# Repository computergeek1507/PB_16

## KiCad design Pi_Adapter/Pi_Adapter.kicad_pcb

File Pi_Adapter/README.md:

# Copyright and Disclaimer
Copyright: Scott Hanson

This documentation describes Open Hardware and is licensed under the CERN OHL v. 1.2.

You may redistribute and modify this documentation under the terms of the CERN OHL v.1.2. (http://ohwr.org/cernohl). This documentation is distributed WITHOUT ANY EXPRESS OR IMPLIED WARRANTY, INCLUDING OF MERCHANTABILITY, SATISFACTORY QUALITY AND FITNESS FOR A PARTICULAR PURPOSE. Please see the CERN OHL v.1.2 for applicable conditions

# Pi Expansion

Expansion breakout for a Raspberry Pi. Open source applications were used to create this PCB. [KiCad](http://kicad.org/) was used for the PCB design, and [LibreOffice](https://www.libreoffice.org/) for the documentation.

To order your own PCB upload the gerber.zip file to your favorite PCB manufacture of choice, I personally use [jlcpcb.com](https://jlcpcb.com/).

### Features
* 16 Port Expansion
* OLED Display header
* 2 pin GPIO Header for Push Button or Relay Support
* 5v Header

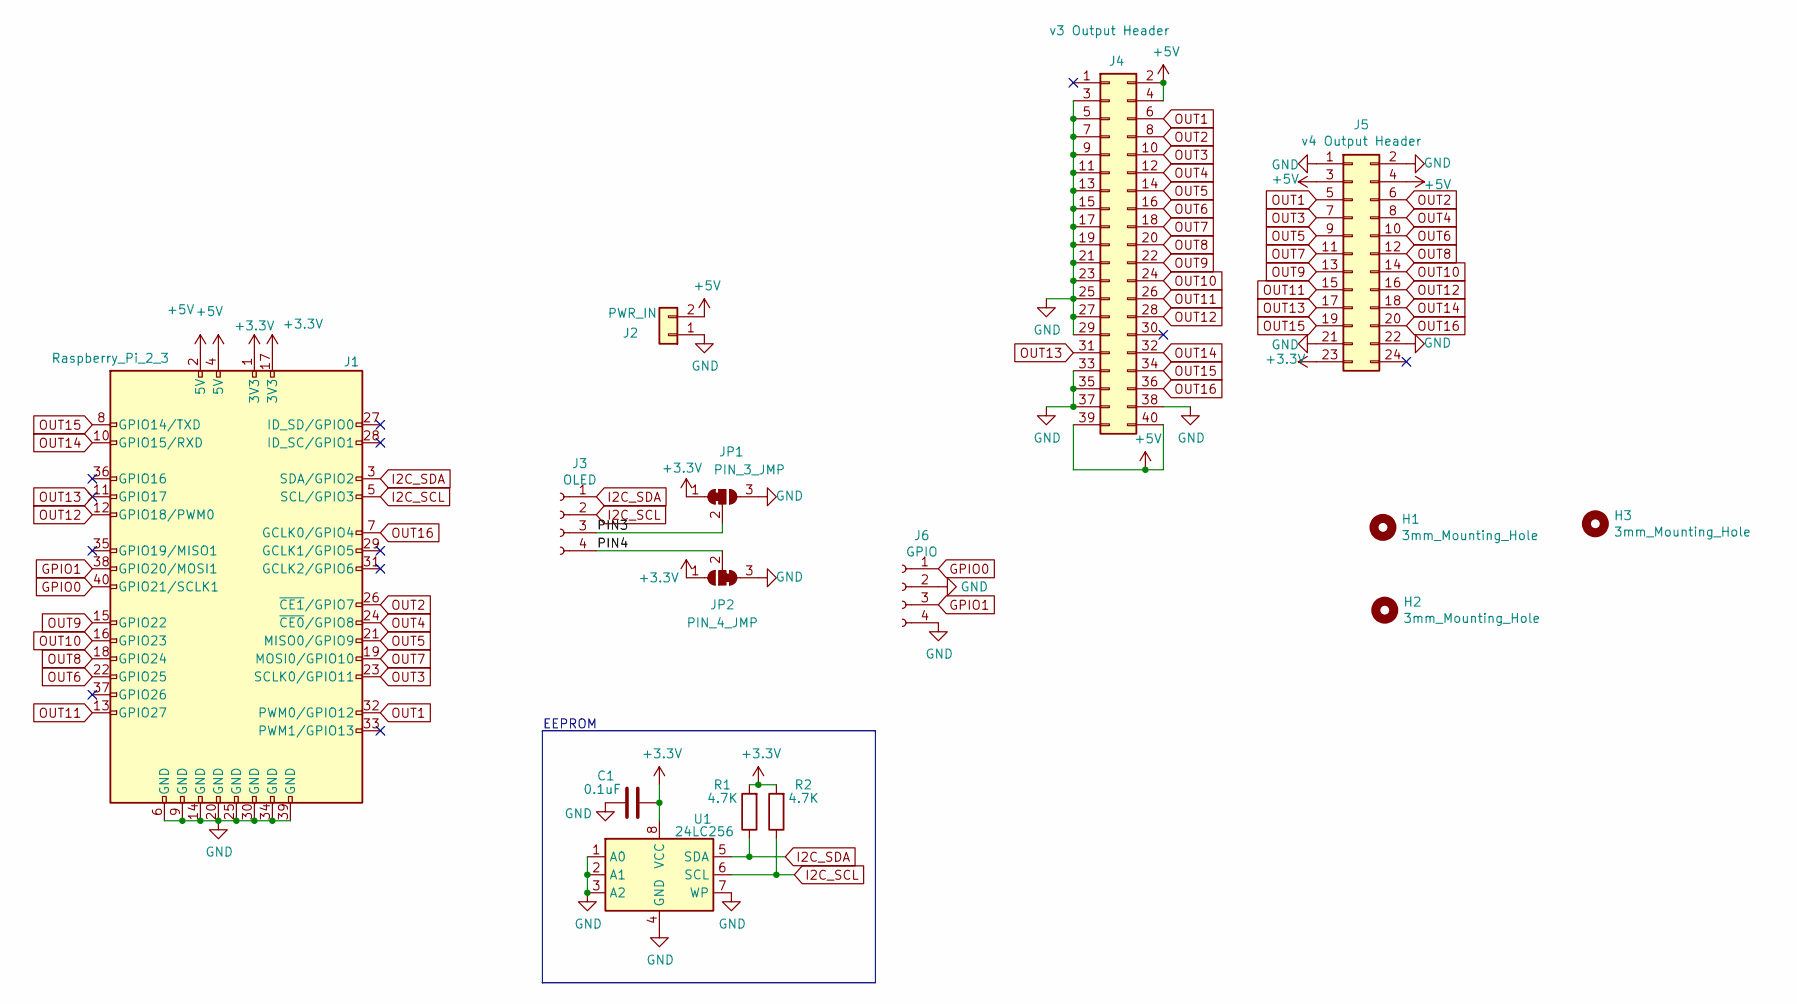
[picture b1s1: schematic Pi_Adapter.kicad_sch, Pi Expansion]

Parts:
C1: 0.1uF; C_0603_1608Metric_Pad1.08x0.95mm_HandSolder; MPN CL10B104KB8NNWC; Digi-Key_PN 1276-1935-2-ND
H1, H2, H3: 3mm_Mounting_Hole; MountingHole_3mm
J1: Raspberry_Pi_2_3; PinSocket_2x20_P2.54mm_Vertical; MPN PPPC202LFBN-RC; Digi-Key_PN S7123-ND
J2: PWR_IN; TerminalBlock_Phoenix_MKDS-1,5-2_1x02_P5.00mm_Horizontal; MPN ED2675-ND; Digi-Key_PN OSTT7020150
J3: OLED; PinSocket_1x04_P2.54mm_Vertical; MPN PPTC041LFBN-RC; Digi-Key_PN S7002-ND
J4: v3 Output Header; IDC-Header_2x20_P2.54mm_Vertical; MPN SBH11-PBPC-D20-ST-BK; Digi-Key_PN S9175-ND
J5: v4 Output Header; IDC-Header_2x12_P2.54mm_Vertical; MPN Z-S311024S1GK1A; Digi-Key_PN ED10525-ND
J6: GPIO; PinSocket_1x04_P2.54mm_Vertical; MPN PPTC041LFBN-RC; Digi-Key_PN S7002-ND
JP1: PIN_3_JMP; SolderJumper-3_P1mm_Bridged12
JP2: PIN_4_JMP; SolderJumper-3_P1mm_Bridged23
R1, R2: 4.7K; R_0603_1608Metric_Pad0.98x0.95mm_HandSolder; MPN RC0603JR-074K7L; Digi-Key_PN 311-4.7KGRCT-ND
U1: 24LC256; SOIC-8_3.9x4.9mm_P1.27mm; MPN 24LC256T-I/SN; Digi-Key_PN 24LC256T-I/SNCT-ND

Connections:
+3V3: C1.1, J1.1 (3V3), J1.17 (3V3), J5.23, JP1.1 (A), JP2.1 (A), R1.2, R2.2, U1.8 (VCC)
+5V: J1.2 (5V), J1.4 (5V), J2.2, J4.2, J4.4, J4.39, J4.40, J5.3, J5.4
/PIN3: J3.3, JP1.2 (C)
/PIN4: J3.4, JP2.2 (C)
GND: C1.2, J1.6 (GND), J1.9 (GND), J1.14 (GND), J1.20 (GND), J1.25 (GND), J1.30 (GND), J1.34 (GND), J1.39 (GND), J2.1, J4.3, J4.5, J4.7, J4.9, J4.11, J4.13, J4.15, J4.17, J4.19, J4.21, J4.23, J4.25, J4.27, J4.29, J4.33, J4.35, J4.37, J4.38, J5.1, J5.2, J5.21, J5.22, J6.2, J6.4, JP1.3 (B), JP2.3 (B), U1.1 (A0), U1.2 (A1), U1.3 (A2), U1.4 (GND), U1.7 (WP)
GPIO0: J1.40 (GPIO21/SCLK1), J6.1
GPIO1: J1.38 (GPIO20/MOSI1), J6.3
I2C_SCL: J1.5 (SCL/GPIO3), J3.2, R2.1, U1.6 (SCL)
I2C_SDA: J1.3 (SDA/GPIO2), J3.1, R1.1, U1.5 (SDA)
OUT1: J1.32 (PWM0/GPIO12), J4.6, J5.5
OUT2: J1.26 (~CE1/GPIO7), J4.8, J5.6
OUT3: J1.23 (SCLK0/GPIO11), J4.10, J5.7
OUT4: J1.24 (~CE0/GPIO8), J4.12, J5.8
OUT5: J1.21 (MISO0/GPIO9), J4.14, J5.9
OUT6: J1.22 (GPIO25), J4.16, J5.10
OUT7: J1.19 (MOSI0/GPIO10), J4.18, J5.11
OUT8: J1.18 (GPIO24), J4.20, J5.12
OUT9: J1.15 (GPIO22), J4.22, J5.13
OUT10: J1.16 (GPIO23), J4.24, J5.14
OUT11: J1.13 (GPIO27), J4.26, J5.15
OUT12: J1.12 (GPIO18/PWM0), J4.28, J5.16
OUT13: J1.11 (GPIO17), J4.31, J5.17
OUT14: J1.10 (GPIO15/RXD), J4.32, J5.18
OUT15: J1.8 (GPIO14/TXD), J4.34, J5.19
OUT16: J1.7 (GCLK0/GPIO4), J4.36, J5.20

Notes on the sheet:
EEPROM

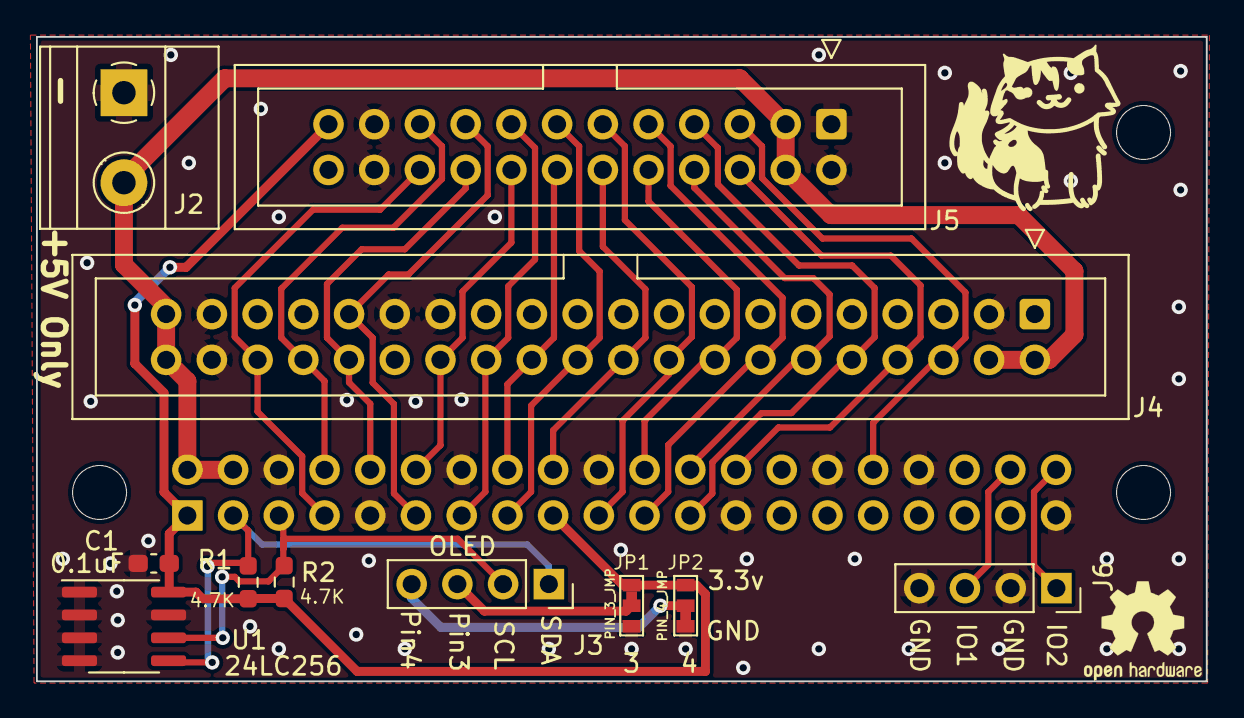
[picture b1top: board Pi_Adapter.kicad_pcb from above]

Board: 2 copper layers, 65.0 x 35.8 mm, 15 parts (1 on the bottom side), 25 nets.

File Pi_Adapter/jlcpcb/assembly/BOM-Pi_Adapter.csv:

Comment,Designator,Footprint,LCSC
0.1uF,C1,C_0603_1608Metric_Pad1.08x0.95mm_HandSolder,C14663
v4 Output Header,J5,IDC-Header_2x12_P2.54mm_Vertical,C221083
4.7K,"R1,R2",R_0603_1608Metric_Pad0.98x0.95mm_HandSolder,C23162
24LC256,U1,SOIC-8_3.9x4.9mm_P1.27mm,C6482
PWR_IN,J2,"TerminalBlock_Phoenix_MKDS-1,5-2_1x02_P5.00mm_Horizontal",
GPIO,J6,PinSocket_1x04_P2.54mm_Vertical,
v3 Output Header,J4,IDC-Header_2x20_P2.54mm_Vertical,
OLED,J3,PinSocket_1x04_P2.54mm_Vertical,
Raspberry_Pi_2_3,J1,PinSocket_2x20_P2.54mm_Vertical,

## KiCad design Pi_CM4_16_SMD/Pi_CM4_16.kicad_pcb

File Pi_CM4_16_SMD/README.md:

# Copyright and Disclaimer
Copyright: Scott Hanson

This documentation describes Open Hardware and is licensed under the CERN Open Hardware Licence Version 2 - Strongly Reciprocal. (CERN-OHL-S)

You may redistribute and modify this documentation under the terms of the CERN OHL-S-v2 (https://ohwr.org/cern_ohl_s_v2.txt). This documentation is distributed WITHOUT ANY EXPRESS OR IMPLIED WARRANTY, INCLUDING OF MERCHANTABILITY, SATISFACTORY QUALITY AND FITNESS FOR A PARTICULAR PURPOSE. Please see the CERN OHL v2-S for applicable conditions

**Under CERN OHL-S-v2, derivative work must be publicy released as defined in subsection 3.3**

# Pi CM4 16

**Never Built or tested**

The Pi CM4 16 is a surface mount(SMD) controller with 16 local pixel ports and one remote receiver port(4 remote ports). A total of 20 pixel outputs. All the design files are open source and available on github.

## [Interactive BOM](https://computergeek1507.github.io/PB_16/Pi_CM4_16_SMD/bom/ibom)

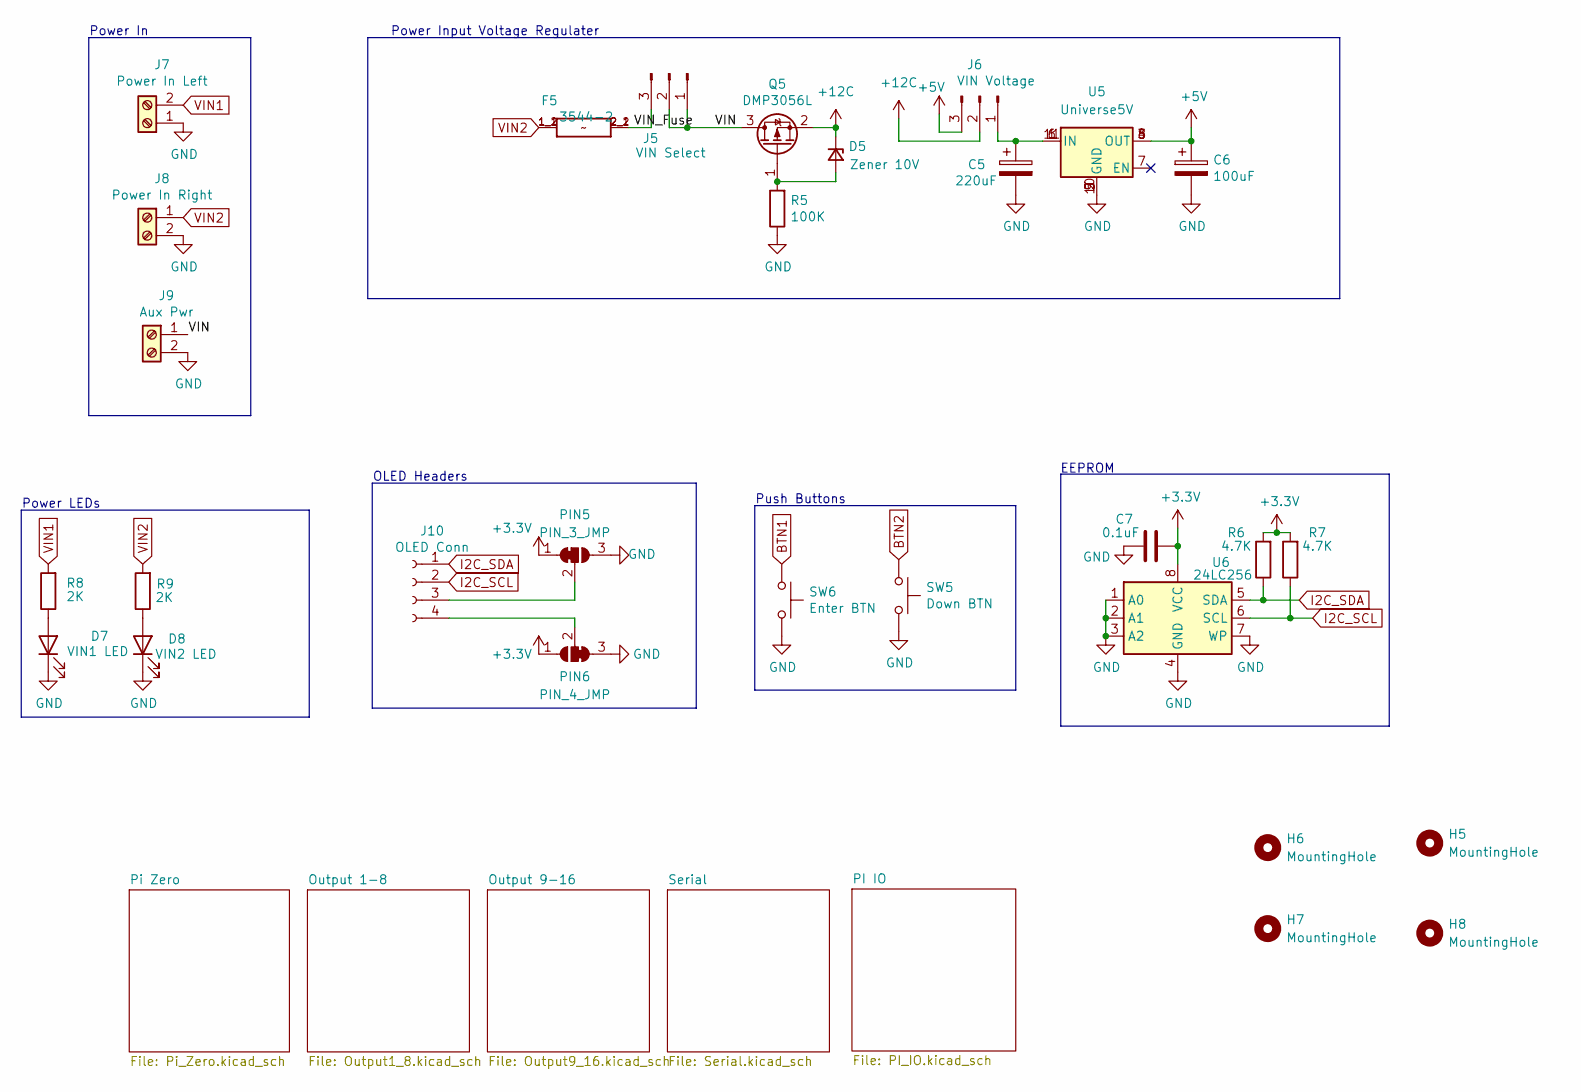
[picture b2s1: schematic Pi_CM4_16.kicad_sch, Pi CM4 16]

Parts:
C5: 220uF; CP_Radial_D10.0mm_P5.00mm; MPN ECA-1HM221; Digi-Key_PN P5183-ND
C6: 100uF; CP_Elec_6.3x5.4_Nichicon; MPN UWX1C101MCL1GB; Digi-Key_PN 493-2105-1-ND
C7: 0.1uF; C_0603_1608Metric_Pad1.08x0.95mm_HandSolder; MPN CL10B104KB8NNWC; Digi-Key_PN 1276-1935-2-ND
D5: Zener 10V; D_SOD-123; MPN MMSZ5240B-7-F; Digi-Key_PN MMSZ5240B-FDICT-ND
D7: VIN1 LED; LED_0603_1608Metric_Pad1.05x0.95mm_HandSolder; MPN LTST-C190KRKT; Digi-Key_PN 160-1436-2-ND
D8: VIN2 LED; LED_0603_1608Metric_Pad1.05x0.95mm_HandSolder; MPN LTST-C190KRKT; Digi-Key_PN 160-1436-2-ND
F5: 3544-2; FUSE_3544-2; MPN 3544-2; Digi-Key_PN 36-3544-2-ND
H5, H6, H7, H8: MountingHole; MountingHole_3.7mm
J5: VIN Select; PinHeader_1x03_P2.54mm_Vertical; MPN 61300311121; Digi-Key_PN 732-5316-ND
J6: VIN Voltage; PinHeader_1x03_P2.54mm_Vertical; MPN 61300311121; Digi-Key_PN 732-5316-ND
J7: Power In Left; BARRIER_BLOCK_1ROW_2POS_P9.5MM; MPN OSTYK51102030; Digi-Key_PN ED2953-ND
J8: Power In Right; BARRIER_BLOCK_1ROW_2POS_P9.5MM; MPN OSTYK51102030; Digi-Key_PN ED2953-ND
J9: Aux Pwr; PHOENIX_MKDS1_2-3.81; MPN 1727010; Digi-Key_PN 277-1947-ND
J10: OLED Conn; PinSocket_1x04_P2.54mm_Vertical; MPN PPTC041LFBN-RC; Digi-Key_PN S7002-ND
PIN5: PIN_3_JMP; SolderJumper-3_P1mm_Bridged12
PIN6: PIN_4_JMP; SolderJumper-3_P1mm_Bridged23
Q5: DMP3056L; SOT-23; MPN DMP3056L-7; Digi-Key_PN DMP3056L-7DICT-ND
R5: 100K; R_0603_1608Metric_Pad0.98x0.95mm_HandSolder; MPN RT0603BRD07100KL; Digi-Key_PN YAG1235CT-ND
R6, R7: 4.7K; R_0603_1608Metric_Pad0.98x0.95mm_HandSolder; MPN RC0603JR-074K7L; Digi-Key_PN 311-4.7KGRCT-ND
R8, R9: 2K; R_0603_1608Metric_Pad0.98x0.95mm_HandSolder
SW5: Down BTN; SW_Push_1P1T_NO_6x6mm_H9.5mm; MPN PTS645SL50SMTR92 LFS; Digi-Key_PN CKN9088CT-ND
SW6: Enter BTN; SW_Push_1P1T_NO_6x6mm_H9.5mm; MPN PTS645SL50SMTR92 LFS; Digi-Key_PN CKN9088CT-ND
U5: Universe5V; Universal_5V_Horizontal
U6: 24LC256; SOIC-8_3.9x4.9mm_P1.27mm; MPN 24LC256T-I/SN; Digi-Key_PN 24LC256T-I/SNCT-ND

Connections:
+3.3V: C7.1, PIN5.1 (A), PIN6.1 (A), R6.2, R7.2, U6.8 (VCC); also elsewhere on the board
+5V: C6.1, J6.3, U5.3 (OUT), U5.4 (OUT), U5.8 (OUT); also elsewhere on the board
+12C: D5.1 (K), J6.2, Q5.2 (S)
/VIN: J5.1, J5.2, J9.1, Q5.3 (D)
/VIN_Fuse: F5.2_1 (2), F5.2_2 (2), J5.3
BTN1: SW6.1; also elsewhere on the board
BTN2: SW5.1; also elsewhere on the board
GND: C5.2, C6.2, C7.2, D7.1 (K), D8.1 (K), J7.1, J8.2, J9.2, PIN5.3 (B), PIN6.3 (B), R5.1, SW5.2, SW6.2, U5.2 (GND), U5.5 (GND), U5.9 (GND), U5.10 (GND), U6.1 (A0), U6.2 (A1), U6.3 (A2), U6.4 (GND), U6.7 (WP); also elsewhere on the board
I2C_SCL: J10.2, R7.1, U6.6 (SCL); also elsewhere on the board
I2C_SDA: J10.1, R6.1, U6.5 (SDA); also elsewhere on the board
unnamed: C5.1, J6.1, U5.1 (IN), U5.6 (IN), U5.11 (IN)
unnamed: D5.2 (A), Q5.1 (G), R5.2
unnamed: D7.2 (A), R8.1
unnamed: D8.2 (A), R9.1
unnamed: J10.3, PIN5.2 (C)
unnamed: J10.4, PIN6.2 (C)
VIN1: J7.2, R8.2; also elsewhere on the board
VIN2: F5.1_1 (1), F5.1_2 (1), J8.1, R9.2; also elsewhere on the board

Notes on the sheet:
Power LEDs
Power In
OLED Headers
Push Buttons
Power Input Voltage Regulater
EEPROM

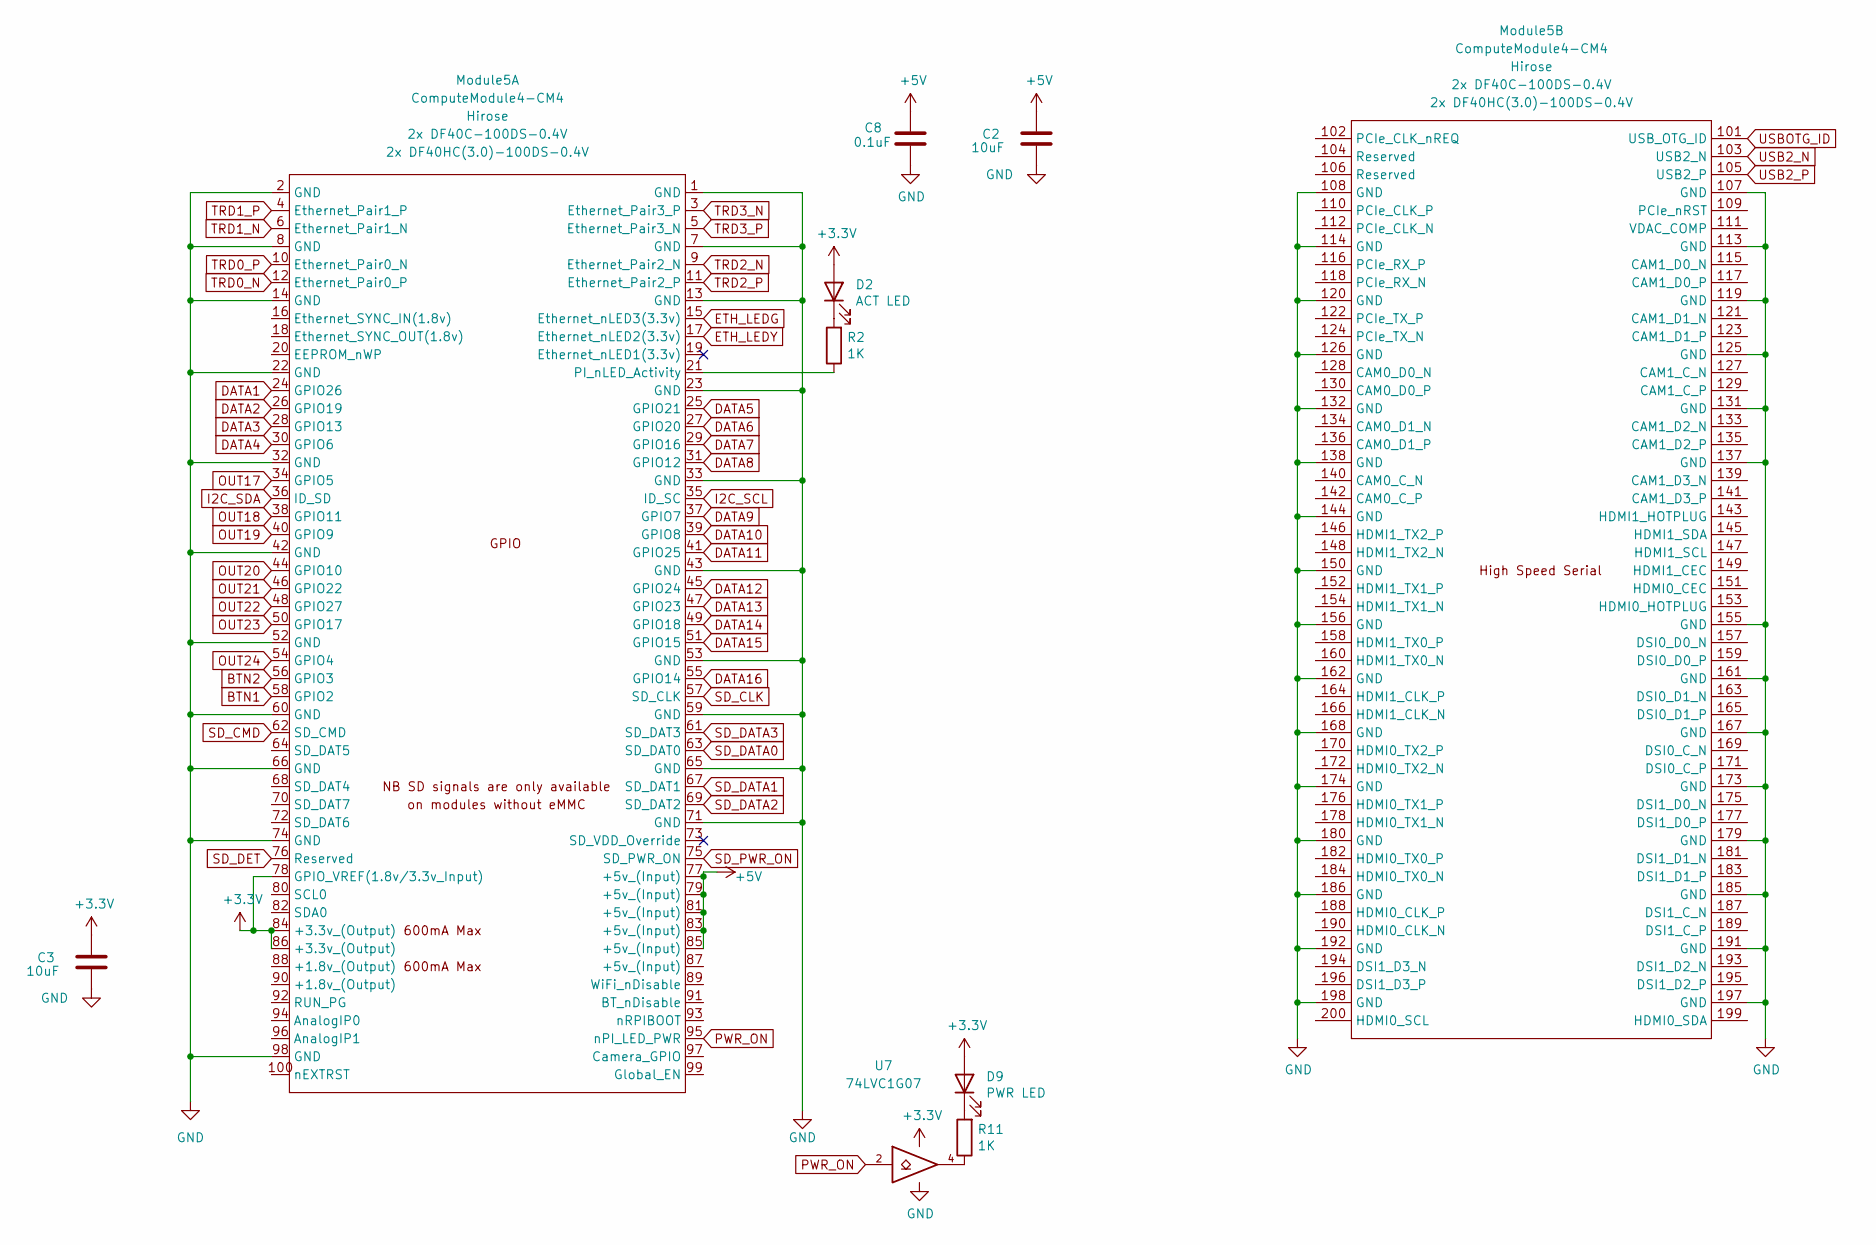
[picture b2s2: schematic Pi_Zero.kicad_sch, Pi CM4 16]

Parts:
C2, C3: 10uF; C_0603_1608Metric_Pad1.08x0.95mm_HandSolder
C8: 0.1uF; C_0603_1608Metric_Pad1.08x0.95mm_HandSolder; MPN CL10B104KB8NNWC; Digi-Key_PN 1276-1935-2-ND
D2: ACT LED; LED_0603_1608Metric_Pad1.05x0.95mm_HandSolder; MPN LTST-C190KRKT; Digi-Key_PN 160-1436-2-ND
D9: PWR LED; LED_0603_1608Metric_Pad1.05x0.95mm_HandSolder; MPN LTST-C190KRKT; Digi-Key_PN 160-1436-2-ND
Module5: ComputeModule4-CM4; Raspberry-Pi-4-Compute-Module; MPN 2x DF40C-100DS-0.4V; Digi-Key_PN 2x H11615CT-ND
R2, R11: 1K; R_0603_1608Metric_Pad0.98x0.95mm_HandSolder
U7: 74LVC1G07; SOT-23-5

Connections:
+3.3V: C3.2, D2.2 (A), D9.2 (A), Module5.78 (GPIO_VREF(1.8v/3.3v_Input)), Module5.84 (+3.3v_(Output)), Module5.86 (+3.3v_(Output)), U7.5 (VCC); also elsewhere on the board
+5V: C2.2, C8.1, Module5.77 (+5v_(Input)), Module5.79 (+5v_(Input)), Module5.81 (+5v_(Input)), Module5.83 (+5v_(Input)), Module5.85 (+5v_(Input)); also elsewhere on the board
BTN1: Module5.58 (GPIO2); also elsewhere on the board
BTN2: Module5.56 (GPIO3); also elsewhere on the board
DATA1: Module5.24 (GPIO26); also elsewhere on the board
DATA2: Module5.26 (GPIO19); also elsewhere on the board
DATA3: Module5.28 (GPIO13); also elsewhere on the board
DATA4: Module5.30 (GPIO6); also elsewhere on the board
DATA5: Module5.25 (GPIO21); also elsewhere on the board
DATA6: Module5.27 (GPIO20); also elsewhere on the board
DATA7: Module5.29 (GPIO16); also elsewhere on the board
DATA8: Module5.31 (GPIO12); also elsewhere on the board
DATA9: Module5.37 (GPIO7); also elsewhere on the board
DATA10: Module5.39 (GPIO8); also elsewhere on the board
DATA11: Module5.41 (GPIO25); also elsewhere on the board
DATA12: Module5.45 (GPIO24); also elsewhere on the board
DATA13: Module5.47 (GPIO23); also elsewhere on the board
DATA14: Module5.49 (GPIO18); also elsewhere on the board
DATA15: Module5.51 (GPIO15); also elsewhere on the board
DATA16: Module5.55 (GPIO14); also elsewhere on the board
ETH_LEDG: Module5.15 (Ethernet_nLED3(3.3v)); also elsewhere on the board
ETH_LEDY: Module5.17 (Ethernet_nLED2(3.3v)); also elsewhere on the board
GND: C2.1, C3.1, C8.2, Module5.1 (GND), Module5.2 (GND), Module5.7 (GND), Module5.8 (GND), Module5.13 (GND), Module5.14 (GND), Module5.22 (GND), Module5.23 (GND), Module5.32 (GND), Module5.33 (GND), Module5.42 (GND), Module5.43 (GND), Module5.52 (GND), Module5.53 (GND), Module5.59 (GND), Module5.60 (GND), Module5.65 (GND), Module5.66 (GND), Module5.71 (GND), Module5.74 (GND), Module5.98 (GND), Module5.107 (GND), Module5.108 (GND), Module5.113 (GND), Module5.114 (GND), Module5.119 (GND), Module5.120 (GND), Module5.125 (GND), Module5.126 (GND), Module5.131 (GND), Module5.132 (GND), Module5.137 (GND), Module5.138 (GND), Module5.144 (GND), Module5.150 (GND), Module5.155 (GND), Module5.156 (GND), Module5.161 (GND), Module5.162 (GND), Module5.167 (GND), Module5.168 (GND), Module5.173 (GND), Module5.174 (GND), Module5.179 (GND), Module5.180 (GND), Module5.185 (GND), Module5.186 (GND), Module5.191 (GND), Module5.192 (GND), Module5.197 (GND), Module5.198 (GND), U7.3 (GND); also elsewhere on the board
I2C_SCL: Module5.35 (ID_SC); also elsewhere on the board
I2C_SDA: Module5.36 (ID_SD); also elsewhere on the board
unnamed: D2.1 (K), R2.2
unnamed: D9.1 (K), R11.2
unnamed: Module5.21 (PI_nLED_Activity), R2.1
unnamed: R11.1, U7.4
OUT17: Module5.34 (GPIO5); also elsewhere on the board
OUT18: Module5.38 (GPIO11); also elsewhere on the board
OUT19: Module5.40 (GPIO9); also elsewhere on the board
OUT20: Module5.44 (GPIO10); also elsewhere on the board
OUT21: Module5.46 (GPIO22)
OUT22: Module5.48 (GPIO27)
OUT23: Module5.50 (GPIO17)
OUT24: Module5.54 (GPIO4)
PWR_ON: Module5.95 (nPI_LED_PWR), U7.2
SD_CLK: Module5.57 (SD_CLK); also elsewhere on the board
SD_CMD: Module5.62 (SD_CMD); also elsewhere on the board
SD_DATA0: Module5.63 (SD_DAT0); also elsewhere on the board
SD_DATA1: Module5.67 (SD_DAT1); also elsewhere on the board
SD_DATA2: Module5.69 (SD_DAT2); also elsewhere on the board
SD_DATA3: Module5.61 (SD_DAT3); also elsewhere on the board
SD_DET: Module5.76 (Reserved); also elsewhere on the board
SD_PWR_ON: Module5.75 (SD_PWR_ON); also elsewhere on the board
TRD0_N: Module5.12 (Ethernet_Pair0_P); also elsewhere on the board
TRD0_P: Module5.10 (Ethernet_Pair0_N); also elsewhere on the board
TRD1_N: Module5.6 (Ethernet_Pair1_N); also elsewhere on the board
TRD1_P: Module5.4 (Ethernet_Pair1_P); also elsewhere on the board
TRD2_N: Module5.9 (Ethernet_Pair2_N); also elsewhere on the board
TRD2_P: Module5.11 (Ethernet_Pair2_P); also elsewhere on the board
TRD3_N: Module5.3 (Ethernet_Pair3_P); also elsewhere on the board
TRD3_P: Module5.5 (Ethernet_Pair3_N); also elsewhere on the board
USB2_N: Module5.103 (USB2_N); also elsewhere on the board
USB2_P: Module5.105 (USB2_P); also elsewhere on the board
USBOTG_ID: Module5.101 (USB_OTG_ID); also elsewhere on the board

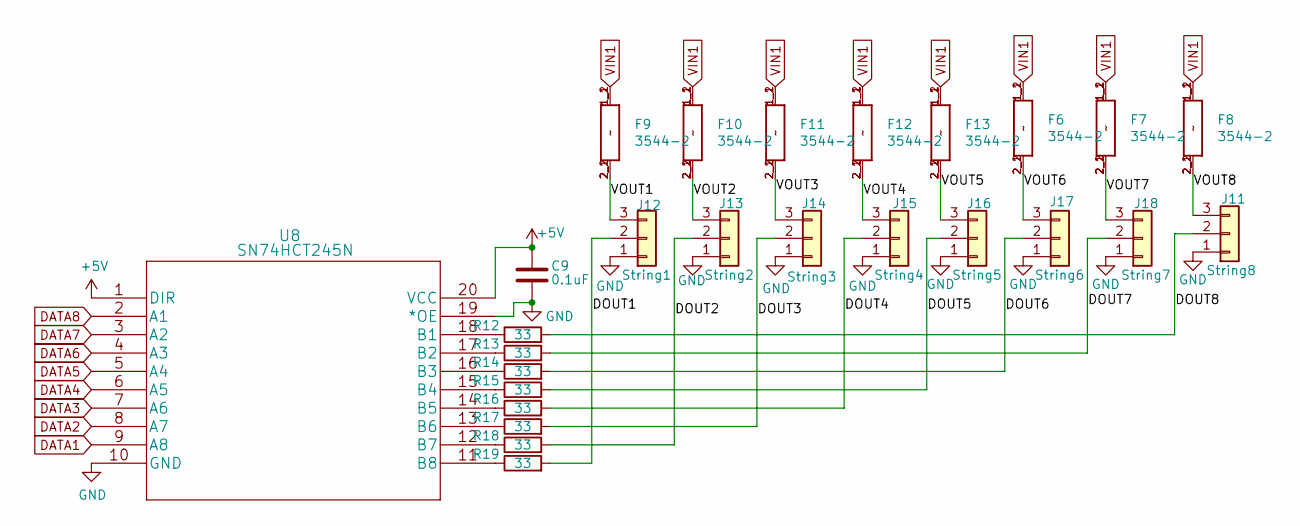
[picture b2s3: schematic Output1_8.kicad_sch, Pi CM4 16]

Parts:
C9: 0.1uF; C_0603_1608Metric_Pad1.08x0.95mm_HandSolder; MPN CL10B104KB8NNWC; Digi-Key_PN 1276-1935-2-ND
F6, F7, F8, F9, F10, F11, F12, F13: 3544-2; FUSE_3544-2; MPN 3544-2; Digi-Key_PN 36-3544-2-ND
J11: String8; PhoenixContact_MCV_3.81mm_3.5mm_1x03_Vertical; MPN 1843619/OSTTJ0311530; Digi-Key_PN 277-5737-ND/ED10555-ND
J12: String1; PhoenixContact_MCV_3.81mm_3.5mm_1x03_Vertical; MPN 1843619/OSTTJ0311530; Digi-Key_PN 277-5737-ND/ED10555-ND
J13: String2; PhoenixContact_MCV_3.81mm_3.5mm_1x03_Vertical; MPN 1843619/OSTTJ0311530; Digi-Key_PN 277-5737-ND/ED10555-ND
J14: String3; PhoenixContact_MCV_3.81mm_3.5mm_1x03_Vertical; MPN 1843619/OSTTJ0311530; Digi-Key_PN 277-5737-ND/ED10555-ND
J15: String4; PhoenixContact_MCV_3.81mm_3.5mm_1x03_Vertical; MPN 1843619/OSTTJ0311530; Digi-Key_PN 277-5737-ND/ED10555-ND
J16: String5; PhoenixContact_MCV_3.81mm_3.5mm_1x03_Vertical; MPN 1843619/OSTTJ0311530; Digi-Key_PN 277-5737-ND/ED10555-ND
J17: String6; PhoenixContact_MCV_3.81mm_3.5mm_1x03_Vertical; MPN 1843619/OSTTJ0311530; Digi-Key_PN 277-5737-ND/ED10555-ND
J18: String7; PhoenixContact_MCV_3.81mm_3.5mm_1x03_Vertical; MPN 1843619/OSTTJ0311530; Digi-Key_PN 277-5737-ND/ED10555-ND
R12, R13, R14, R15, R16, R17, R18, R19: 33; R_0603_1608Metric_Pad0.98x0.95mm_HandSolder; MPN RC0603FR-0733RL; LCSC C23140
U8: SN74HCT245N; SN74HCT245NSR; MPN SN74HCT245NSR; Digi-Key_PN 296-15849-1-ND

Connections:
+5V: C9.1, U8.1 (DIR), U8.20 (VCC); also elsewhere on the board
/Output 1-8/DOUT1: J12.2, R19.2
/Output 1-8/DOUT2: J13.2, R18.2
/Output 1-8/DOUT3: J14.2, R17.2
/Output 1-8/DOUT4: J15.2, R16.2
/Output 1-8/DOUT5: J16.2, R15.2
/Output 1-8/DOUT6: J17.2, R14.2
/Output 1-8/DOUT7: J18.2, R13.2
/Output 1-8/DOUT8: J11.2, R12.2
/Output 1-8/VOUT1: F9.2_1 (2), F9.2_2 (2), J12.3
/Output 1-8/VOUT2: F10.2_1 (2), F10.2_2 (2), J13.3
/Output 1-8/VOUT3: F11.2_1 (2), F11.2_2 (2), J14.3
/Output 1-8/VOUT4: F12.2_1 (2), F12.2_2 (2), J15.3
/Output 1-8/VOUT5: F13.2_1 (2), F13.2_2 (2), J16.3
/Output 1-8/VOUT6: F6.2_1 (2), F6.2_2 (2), J17.3
/Output 1-8/VOUT7: F7.2_1 (2), F7.2_2 (2), J18.3
/Output 1-8/VOUT8: F8.2_1 (2), F8.2_2 (2), J11.3
DATA1: U8.9 (A8); also elsewhere on the board
DATA2: U8.8 (A7); also elsewhere on the board
DATA3: U8.7 (A6); also elsewhere on the board
DATA4: U8.6 (A5); also elsewhere on the board
DATA5: U8.5 (A4); also elsewhere on the board
DATA6: U8.4 (A3); also elsewhere on the board
DATA7: U8.3 (A2); also elsewhere on the board
DATA8: U8.2 (A1); also elsewhere on the board
GND: C9.2, J11.1, J12.1, J13.1, J14.1, J15.1, J16.1, J17.1, J18.1, U8.10 (GND), U8.19 (*OE); also elsewhere on the board
unnamed: R12.1, U8.18 (B1)
unnamed: R13.1, U8.17 (B2)
unnamed: R14.1, U8.16 (B3)
unnamed: R15.1, U8.15 (B4)
unnamed: R16.1, U8.14 (B5)
unnamed: R17.1, U8.13 (B6)
unnamed: R18.1, U8.12 (B7)
unnamed: R19.1, U8.11 (B8)
VIN1: F6.1_1 (1), F6.1_2 (1), F7.1_1 (1), F7.1_2 (1), F8.1_1 (1), F8.1_2 (1), F9.1_1 (1), F9.1_2 (1), F10.1_1 (1), F10.1_2 (1), F11.1_1 (1), F11.1_2 (1), F12.1_1 (1), F12.1_2 (1), F13.1_1 (1), F13.1_2 (1); also elsewhere on the board

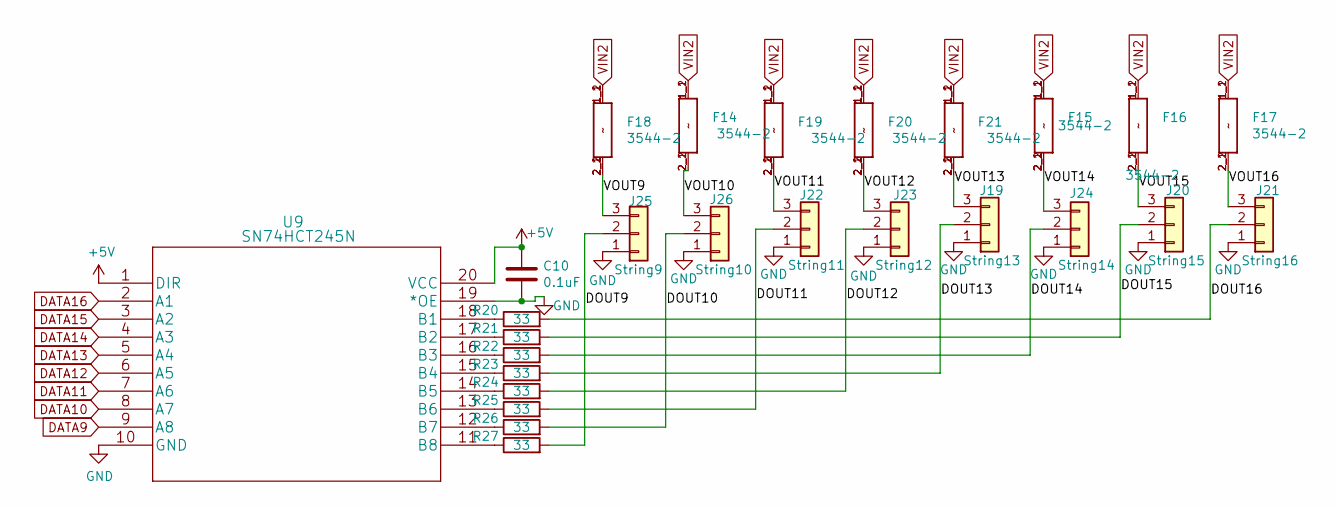
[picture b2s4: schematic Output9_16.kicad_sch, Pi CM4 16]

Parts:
C10: 0.1uF; C_0603_1608Metric_Pad1.08x0.95mm_HandSolder; MPN CL10B104KB8NNWC; Digi-Key_PN 1276-1935-2-ND
F14, F15, F16, F17, F18, F19, F20, F21: 3544-2; FUSE_3544-2; MPN 3544-2; Digi-Key_PN 36-3544-2-ND
J19: String13; PhoenixContact_MCV_3.81mm_3.5mm_1x03_Vertical; MPN 1843619/OSTTJ0311530; Digi-Key_PN 277-5737-ND/ED10555-ND
J20: String15; PhoenixContact_MCV_3.81mm_3.5mm_1x03_Vertical; MPN 1843619/OSTTJ0311530; Digi-Key_PN 277-5737-ND/ED10555-ND
J21: String16; PhoenixContact_MCV_3.81mm_3.5mm_1x03_Vertical; MPN 1843619/OSTTJ0311530; Digi-Key_PN 277-5737-ND/ED10555-ND
J22: String11; PhoenixContact_MCV_3.81mm_3.5mm_1x03_Vertical; MPN 1843619/OSTTJ0311530; Digi-Key_PN 277-5737-ND/ED10555-ND
J23: String12; PhoenixContact_MCV_3.81mm_3.5mm_1x03_Vertical; MPN 1843619/OSTTJ0311530; Digi-Key_PN 277-5737-ND/ED10555-ND
J24: String14; PhoenixContact_MCV_3.81mm_3.5mm_1x03_Vertical; MPN 1843619/OSTTJ0311530; Digi-Key_PN 277-5737-ND/ED10555-ND
J25: String9; PhoenixContact_MCV_3.81mm_3.5mm_1x03_Vertical; MPN 1843619/OSTTJ0311530; Digi-Key_PN 277-5737-ND/ED10555-ND
J26: String10; PhoenixContact_MCV_3.81mm_3.5mm_1x03_Vertical; MPN 1843619/OSTTJ0311530; Digi-Key_PN 277-5737-ND/ED10555-ND
R20, R21, R22, R23, R24, R25, R26, R27: 33; R_0603_1608Metric_Pad0.98x0.95mm_HandSolder; MPN RC0603FR-0733RL; LCSC C23140
U9: SN74HCT245N; SN74HCT245NSR; MPN SN74HCT245NSR; Digi-Key_PN 296-15849-1-ND

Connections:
+5V: C10.1, U9.1 (DIR), U9.20 (VCC); also elsewhere on the board
/Output 9-16/DOUT9: J25.2, R27.2
/Output 9-16/DOUT10: J26.2, R26.2
/Output 9-16/DOUT11: J22.2, R25.2
/Output 9-16/DOUT12: J23.2, R24.2
/Output 9-16/DOUT13: J19.2, R23.2
/Output 9-16/DOUT14: J24.2, R22.2
/Output 9-16/DOUT15: J20.2, R21.2
/Output 9-16/DOUT16: J21.2, R20.2
/Output 9-16/VOUT9: F18.2_1 (2), F18.2_2 (2), J25.3
/Output 9-16/VOUT10: F14.2_1 (2), F14.2_2 (2), J26.3
/Output 9-16/VOUT11: F19.2_1 (2), F19.2_2 (2), J22.3
/Output 9-16/VOUT12: F20.2_1 (2), F20.2_2 (2), J23.3
/Output 9-16/VOUT13: F21.2_1 (2), F21.2_2 (2), J19.3
/Output 9-16/VOUT14: F15.2_1 (2), F15.2_2 (2), J24.3
/Output 9-16/VOUT15: F16.2_1 (2), F16.2_2 (2), J20.3
/Output 9-16/VOUT16: F17.2_1 (2), F17.2_2 (2), J21.3
DATA9: U9.9 (A8); also elsewhere on the board
DATA10: U9.8 (A7); also elsewhere on the board
DATA11: U9.7 (A6); also elsewhere on the board
DATA12: U9.6 (A5); also elsewhere on the board
DATA13: U9.5 (A4); also elsewhere on the board
DATA14: U9.4 (A3); also elsewhere on the board
DATA15: U9.3 (A2); also elsewhere on the board
DATA16: U9.2 (A1); also elsewhere on the board
GND: C10.2, J19.1, J20.1, J21.1, J22.1, J23.1, J24.1, J25.1, J26.1, U9.10 (GND), U9.19 (*OE); also elsewhere on the board
unnamed: R20.1, U9.18 (B1)
unnamed: R21.1, U9.17 (B2)
unnamed: R22.1, U9.16 (B3)
unnamed: R23.1, U9.15 (B4)
unnamed: R24.1, U9.14 (B5)
unnamed: R25.1, U9.13 (B6)
unnamed: R26.1, U9.12 (B7)
unnamed: R27.1, U9.11 (B8)
VIN2: F14.1_1 (1), F14.1_2 (1), F15.1_1 (1), F15.1_2 (1), F16.1_1 (1), F16.1_2 (1), F17.1_1 (1), F17.1_2 (1), F18.1_1 (1), F18.1_2 (1), F19.1_1 (1), F19.1_2 (1), F20.1_1 (1), F20.1_2 (1), F21.1_1 (1), F21.1_2 (1); also elsewhere on the board

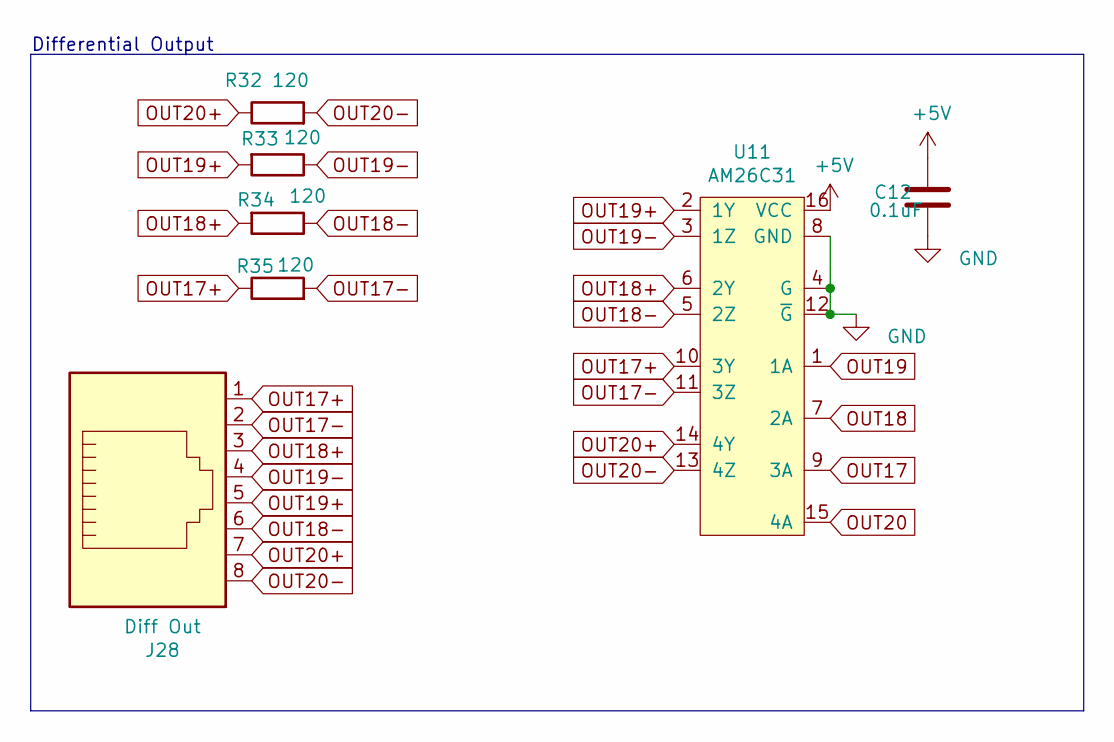
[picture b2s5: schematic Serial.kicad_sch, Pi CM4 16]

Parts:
C12: 0.1uF; C_0603_1608Metric_Pad1.08x0.95mm_HandSolder; MPN CL10B104KB8NNWC; Digi-Key_PN 1276-1935-2-ND
J28: Diff Out; RJ45_Amphenol_54602-x08_Horizontal; MPN X05ADIWA1DY1022; Digi-Key_PN AE10392-ND
R32, R33, R34, R35: 120; R_0603_1608Metric_Pad0.98x0.95mm_HandSolder; MPN CRGCQ0603F120R; Digi-Key_PN A129677CT-ND
U11: AM26C31; SOIC-16_3.9x9.9mm_P1.27mm; MPN AM26C31IDR; Farnell 4975637

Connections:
+5V: C12.1, U11.16 (VCC); also elsewhere on the board
GND: C12.2, U11.4 (G), U11.8 (GND), U11.12 (~G); also elsewhere on the board
OUT17: U11.9 (3A); also elsewhere on the board
OUT17+: J28.1, R35.1, U11.10 (3Y)
OUT17-: J28.2, R35.2, U11.11 (3Z)
OUT18: U11.7 (2A); also elsewhere on the board
OUT18+: J28.3, R34.2, U11.6 (2Y)
OUT18-: J28.6, R34.1, U11.5 (2Z)
OUT19: U11.1 (1A); also elsewhere on the board
OUT19+: J28.5, R33.2, U11.2 (1Y)
OUT19-: J28.4, R33.1, U11.3 (1Z)
OUT20: U11.15 (4A); also elsewhere on the board
OUT20+: J28.7, R32.1, U11.14 (4Y)
OUT20-: J28.8, R32.2, U11.13 (4Z)

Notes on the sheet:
Differential Output

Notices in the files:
parts and their libraries:
Copyright 2016 Accelerated Designs. All rights reserved.
